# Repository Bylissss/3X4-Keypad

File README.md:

# 3X4-Keypad
Kicad project that i do while couldn't sleep

Holy there is a gitignore template for Kicad 

# Known issues

Turns out SW_Push switch that i use doesn't have a footprint which causes to pcb to not work

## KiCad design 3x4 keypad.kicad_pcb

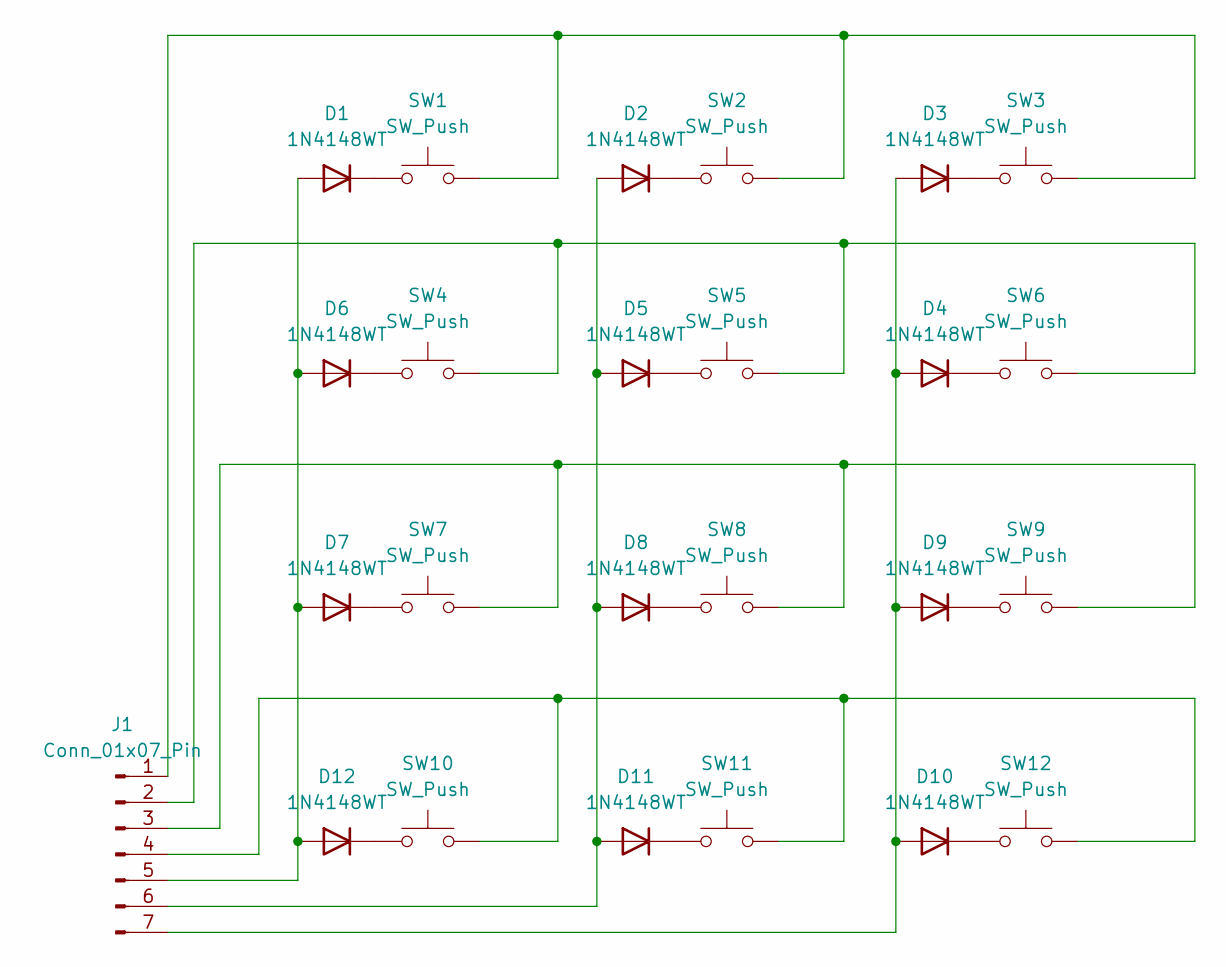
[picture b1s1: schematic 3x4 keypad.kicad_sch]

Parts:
D1, D2, D3, D4, D5, D6, D7, D8, D9, D10, D11, D12: 1N4148WT; D_SOD-523
J1: Conn_01x07_Pin; Hirose_DF13-07P-1.25DS_1x07_P1.25mm_Horizontal
SW1, SW2, SW3, SW4, SW5, SW6, SW7, SW8, SW9, SW10, SW11, SW12: SW_Push; SW_CW_GPTS203211B

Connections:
unnamed: D1.2 (A), D6.2 (A), D7.2 (A), D12.2 (A), J1.5
unnamed: D1.1 (K), SW1.1
unnamed: D2.1 (K), SW2.1
unnamed: D3.1 (K), SW3.1
unnamed: D4.1 (K), SW6.1
unnamed: D5.1 (K), SW5.1
unnamed: D6.1 (K), SW4.1
unnamed: D7.1 (K), SW7.1
unnamed: D8.1 (K), SW8.1
unnamed: D9.1 (K), SW9.1
unnamed: D3.2 (A), D4.2 (A), D9.2 (A), D10.2 (A), J1.7
unnamed: D10.1 (K), SW12.1
unnamed: D2.2 (A), D5.2 (A), D8.2 (A), D11.2 (A), J1.6
unnamed: D11.1 (K), SW11.1
unnamed: D12.1 (K), SW10.1
unnamed: J1.1, SW1.2, SW2.2, SW3.2
unnamed: J1.2, SW4.2, SW5.2, SW6.2
unnamed: J1.3, SW7.2, SW8.2, SW9.2
unnamed: J1.4, SW10.2, SW11.2, SW12.2

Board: 2 copper layers, 25 parts (0 on the bottom side), 19 nets, no tracks yet.
